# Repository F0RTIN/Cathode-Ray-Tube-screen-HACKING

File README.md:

# CRT Audio Reactive Hack

This project explores analog modifications of a Cathode Ray Tube (CRT) display to enable manual and experimental control over image deformation and color channels.

## Safety Warning

CRT displays operate at high voltages (several kilovolts) and can retain charge even when powered off.

- Risk of electric shock
- Dangerous stored energy
- Only attempt if properly trained

Always discharge the CRT before handling.

---

## Project Goals

- Control RGB channels manually
- Modify vertical image scaling
- Experiment with audio-reactive image deformation (prototype)

---

## Hardware Modifications

### RGB Channel Control

For each RGB channel:

- Replace the original resistor (e.g. R903 for Red) with:
  - a 10kΩ potentiometer
  - a 1kΩ resistor in parallel

Purpose:
- Enable adjustable intensity
- Prevent unsafe low resistance values

---

### Vertical Compression

- Replace resistor R350 with a 10kΩ potentiometer

Effect:
- Adjust vertical deflection amplitude
- Compress or stretch the image vertically

---

## Audio Reactive System (Experimental)

A prototype circuit was designed:

1. Audio input
2. Low-pass filter
3. Amplification stage
4. Comparator
5. Injection into horizontal deflection

Result:
- Non-functional
- Unstable behavior

See `/schematics/` for details.

---

## Results

(Add images here)

---

## Documentation

- docs/theory.md
- docs/modifications.md
- docs/troubleshooting.md

---

## Limitations

- Audio system not working
- Behavior depends on CRT model
- Requires manual tuning

---

## License

Open-source hardware / documentation

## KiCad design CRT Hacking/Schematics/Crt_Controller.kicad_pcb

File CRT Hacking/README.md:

# CRT Audio Reactive Hack

This project explores analog modifications of a Cathode Ray Tube (CRT) display to enable manual and experimental control over image deformation and color channels.

## Safety Warning

CRT displays operate at high voltages (several kilovolts) and can retain charge even when powered off.

- Risk of electric shock
- Dangerous stored energy
- Only attempt if properly trained

Always discharge the CRT before handling.

---

## Project Goals

- Control RGB channels manually
- Modify vertical image scaling
- Experiment with audio-reactive image deformation (prototype)

---

## Hardware Modifications

### RGB Channel Control

For each RGB channel:

- Replace the original resistor (e.g. R903 for Red) with:
  - a 10kΩ potentiometer
  - a 1kΩ resistor in parallel

Purpose:
- Enable adjustable intensity
- Prevent unsafe low resistance values

---

### Vertical Compression

- Replace resistor R350 with a 10kΩ potentiometer

Effect:
- Adjust vertical deflection amplitude
- Compress or stretch the image vertically

---

## Audio Reactive System (Experimental)

A prototype circuit was designed:

1. Audio input
2. Low-pass filter
3. Amplification stage
4. Comparator
5. Injection into horizontal deflection

Result:
- Non-functional
- Unstable behavior

See `/schematics/` for details.

---

## Results

(Add images here)

---

## Documentation

- docs/theory.md
- docs/modifications.md
- docs/troubleshooting.md

---

## Limitations

- Audio system not working
- Behavior depends on CRT model
- Requires manual tuning

---

## License

Open-source hardware / documentation

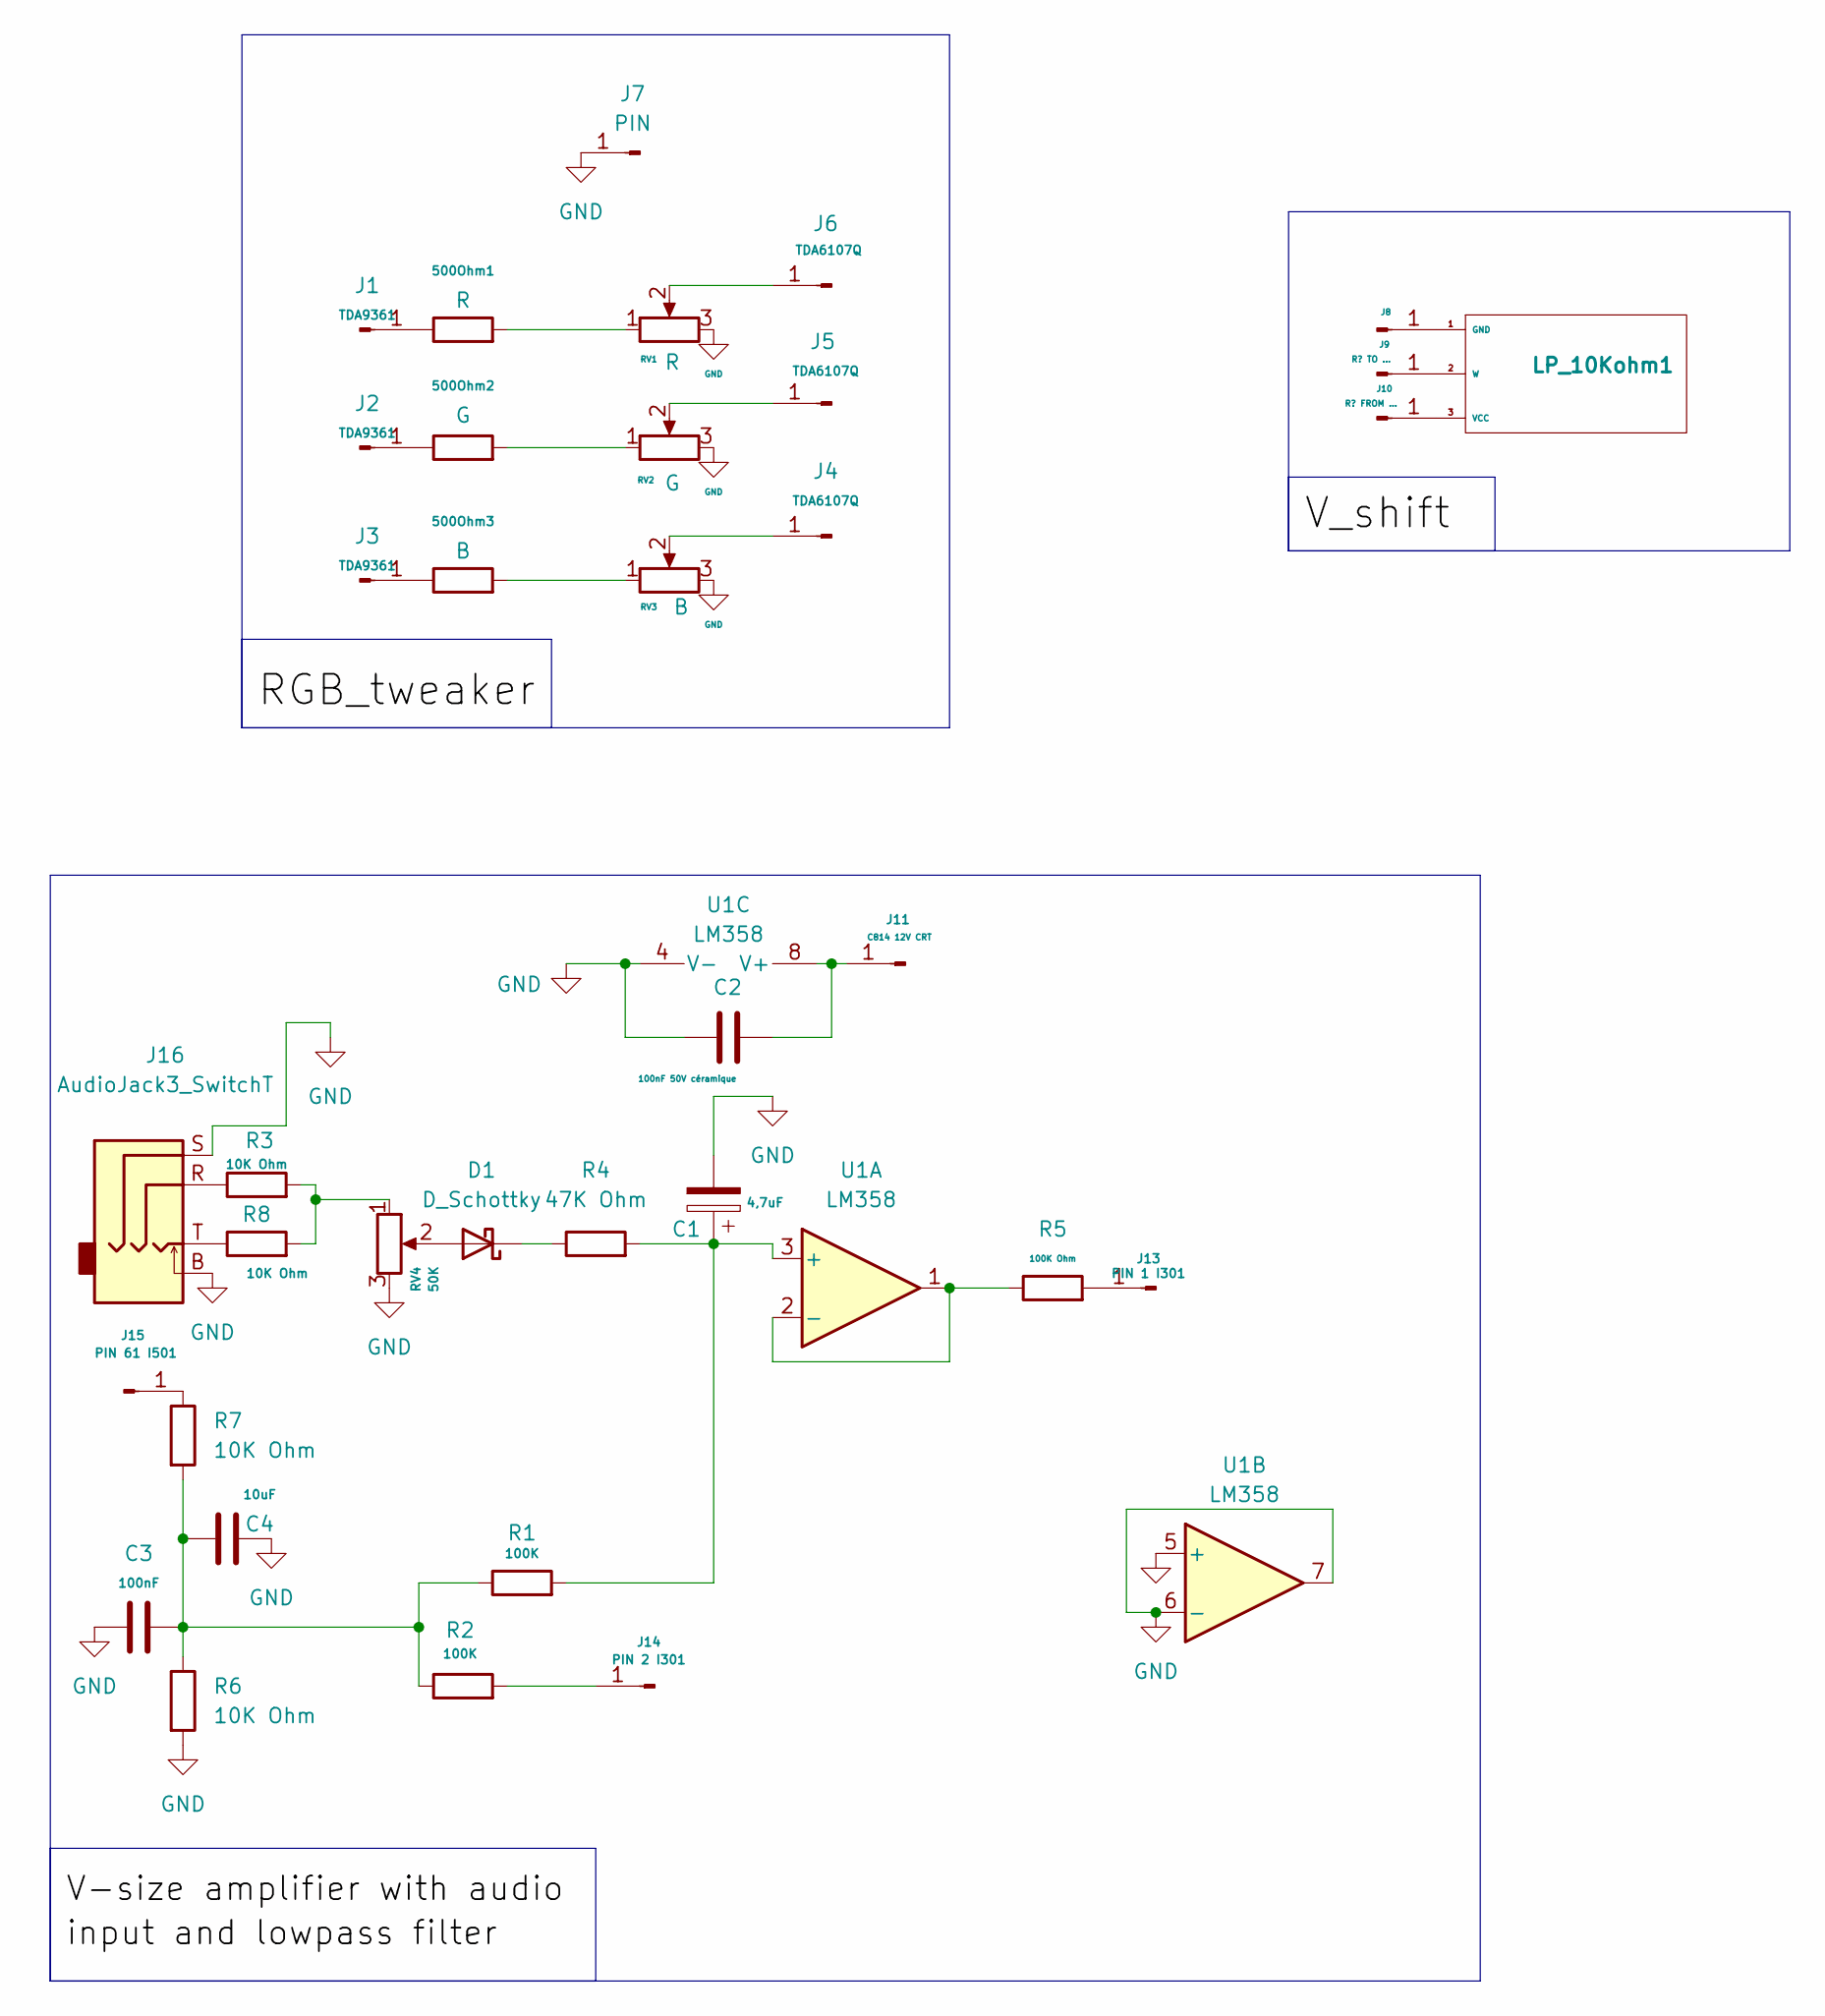
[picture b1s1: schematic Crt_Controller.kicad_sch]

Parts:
500Ohm1: R; R_Axial_DIN0207_L6.3mm_D2.5mm_P7.62mm_Horizontal
500Ohm2: G; R_Axial_DIN0207_L6.3mm_D2.5mm_P7.62mm_Horizontal
500Ohm3: B; R_Axial_DIN0207_L6.3mm_D2.5mm_P7.62mm_Horizontal
C1: 4,7uF; CP_Radial_D5.0mm_P2.00mm
C2: 100nF 50V céramique; C_Disc_D5.0mm_W2.5mm_P5.00mm
C3: 100nF; C_Disc_D5.0mm_W2.5mm_P5.00mm
C4: 10uF; C_Disc_D5.0mm_W2.5mm_P5.00mm
D1: D_Schottky; SOT-23
J1, J2, J3: TDA9361; SolderWirePad_1x01_SMD_1x2mm
J4, J5, J6: TDA6107Q; SolderWirePad_1x01_SMD_1x2mm
J7: PIN; SolderWirePad_1x01_SMD_2x4mm
J8, J10: R? FROM ...; SolderWirePad_1x01_SMD_2x4mm
J9: R? TO ...; SolderWirePad_1x01_SMD_2x4mm
J11: C814 12V CRT; SolderWirePad_1x01_SMD_1x2mm
J13: PIN 1 I301; SolderWirePad_1x01_SMD_1x2mm
J14: PIN 2 I301; SolderWirePad_1x01_SMD_1x2mm
J15: PIN 61 I501; SolderWirePad_1x01_SMD_1x2mm
J16: AudioJack3_SwitchT; KLBR4
LP_10Kohm1: Slider_10Kohm
R1, R2: 100K; R_Axial_DIN0207_L6.3mm_D2.5mm_P10.16mm_Horizontal
R3, R6, R7, R8: 10K Ohm; R_Axial_DIN0207_L6.3mm_D2.5mm_P10.16mm_Horizontal
R4: 47K Ohm; R_Axial_DIN0207_L6.3mm_D2.5mm_P10.16mm_Horizontal
R5: 100K Ohm; R_Axial_DIN0207_L6.3mm_D2.5mm_P10.16mm_Horizontal
RV1: R; Potentiometer_Alps_RK09K_Single_Vertical
RV2: G; Potentiometer_Alps_RK09K_Single_Vertical
RV3: B; Potentiometer_Alps_RK09K_Single_Vertical
RV4: 50K; Potentiometer_Alps_RK09K_Single_Vertical
U1: LM358; SOIC-8_3.9x4.9mm_P1.27mm

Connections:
GND: C1.2, C2.2, C3.1, C4.1, J7.1, J16.B, J16.S, R6.2, RV1.3, RV2.3, RV3.3, RV4.3, U1.4 (V-), U1.5 (+), U1.6 (-), U1.7
unnamed: 500Ohm1.2, RV1.1
unnamed: 500Ohm2.2, RV2.1
unnamed: 500Ohm3.2, RV3.1
unnamed: C3.2, C4.2, R1.1, R2.1, R6.1, R7.2
unnamed: D1.2 (A), RV4.2
unnamed: D1.1 (K), R4.1
unnamed: 500Ohm1.1, J1.1
unnamed: 500Ohm2.1, J2.1
unnamed: 500Ohm3.1, J3.1
unnamed: J4.1, RV3.2
unnamed: J5.1, RV2.2
unnamed: J6.1, RV1.2
unnamed: J8.1, LP_10Kohm1.1 (GND)
unnamed: J9.1, LP_10Kohm1.2 (W)
unnamed: J10.1, LP_10Kohm1.3 (VCC)
unnamed: C2.1, J11.1, U1.8 (V+)
unnamed: J13.1, R5.2
unnamed: J14.1, R2.2
unnamed: J15.1, R7.1
unnamed: J16.R, R3.1
unnamed: J16.T, R8.1
unnamed: R3.2, R8.2, RV4.1
unnamed: C1.1, R1.2, R4.2, U1.3 (+)
unnamed: R5.1, U1.1, U1.2 (-)

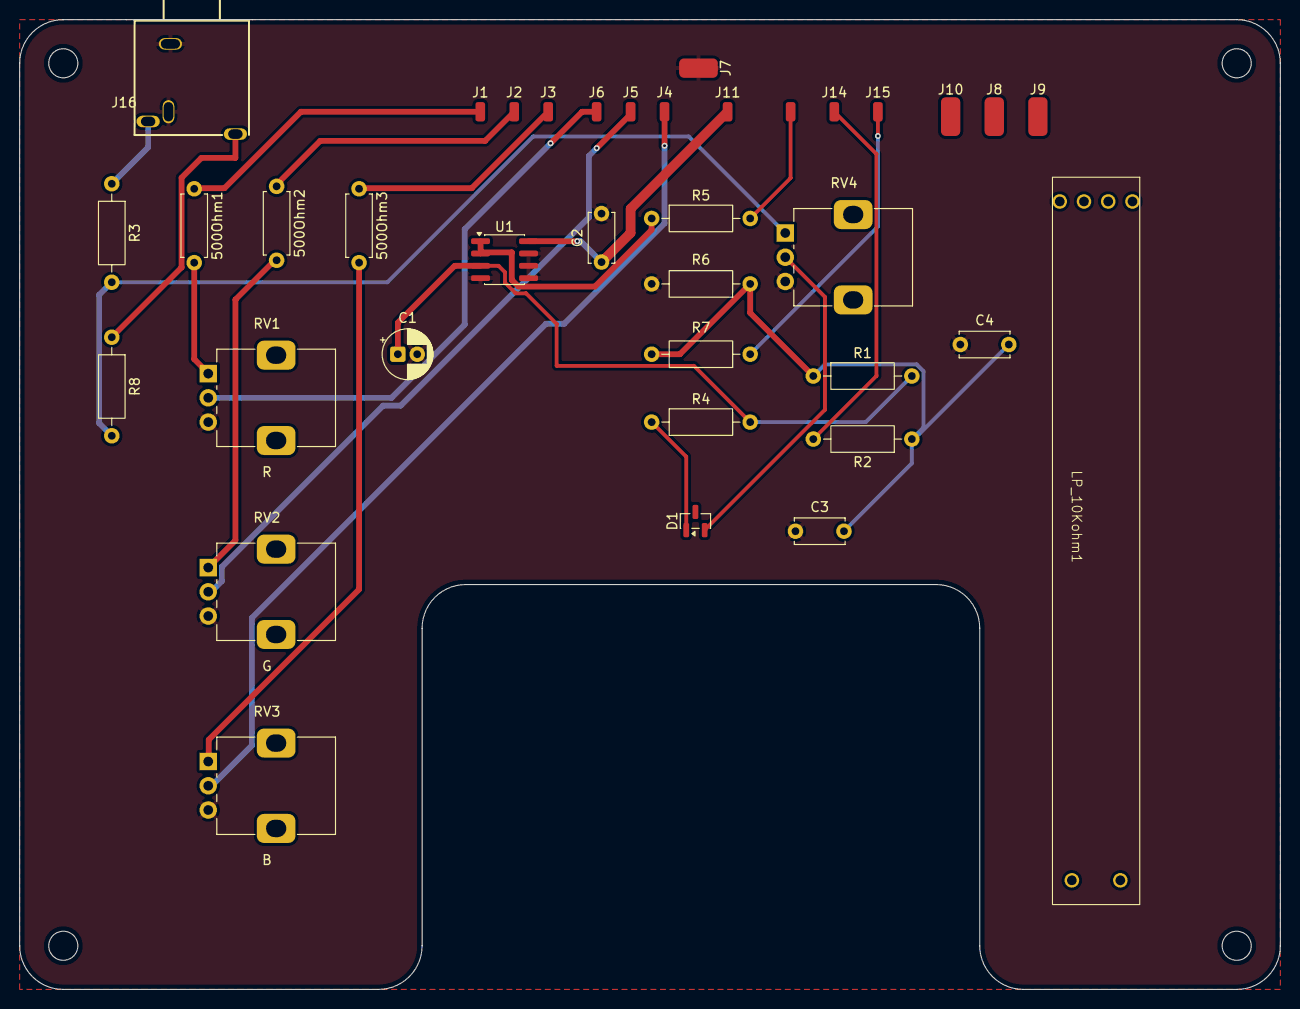
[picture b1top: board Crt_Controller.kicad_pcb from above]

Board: 2 copper layers, 130.0 x 100.0 mm, 37 parts (0 on the bottom side), 25 nets.

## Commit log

2026-04-14 Add README for CRT Audio Reactive Hack project
    This README outlines the CRT Audio Reactive Hack project, including safety warnings, project goals, hardware modifications, an experimental audio reactive system, results, documentation, limitations,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
